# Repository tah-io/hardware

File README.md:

This repository consists of all the hardware design files for Tah

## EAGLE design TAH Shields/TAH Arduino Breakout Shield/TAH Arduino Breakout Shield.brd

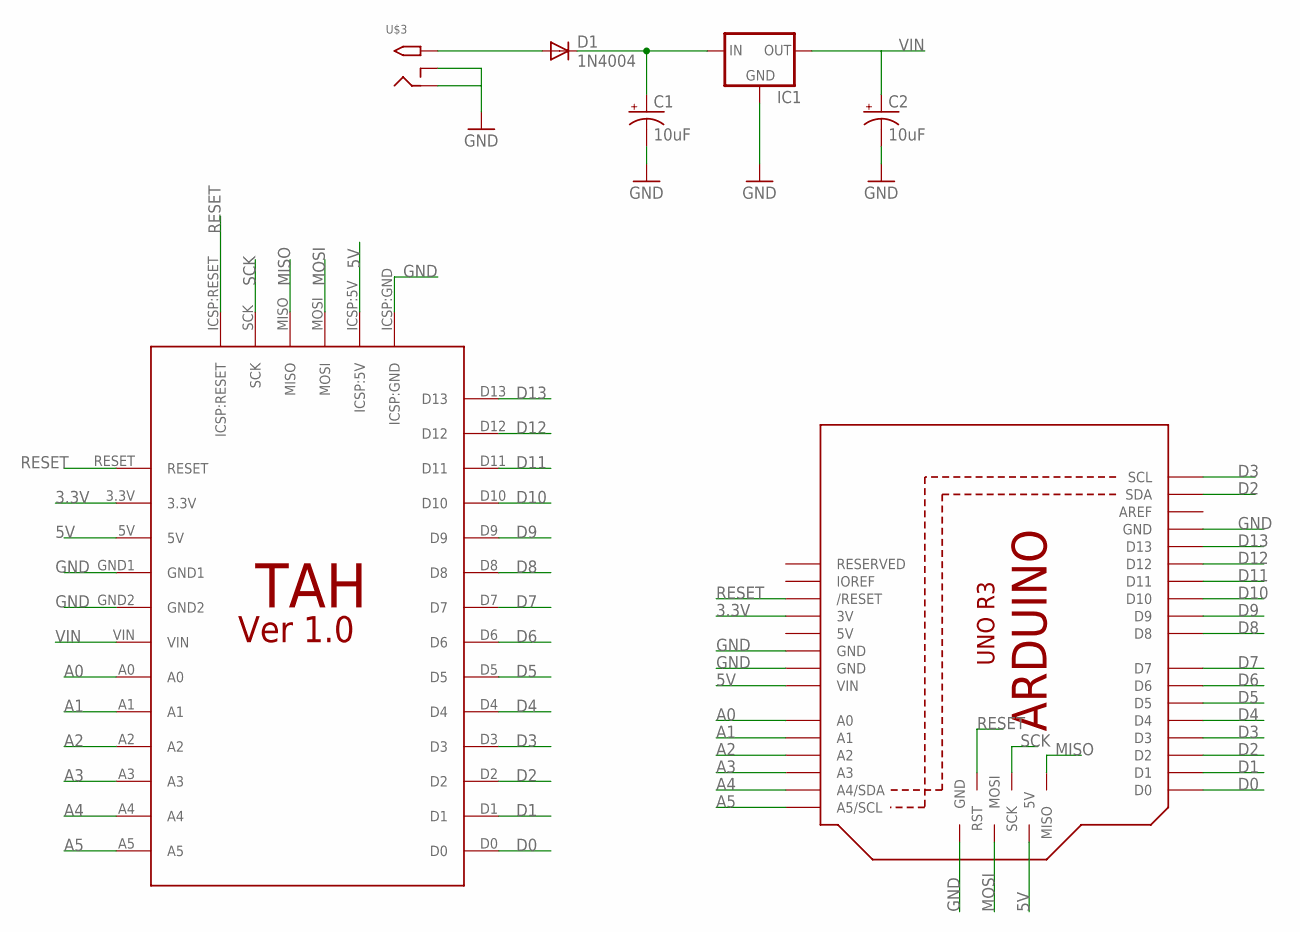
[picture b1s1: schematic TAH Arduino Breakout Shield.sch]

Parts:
C1, C2: 10uF; E2,5-6E
D1: 1N4004; DO41-10
IC1: V_REG_78XX-TO-220; TO-220-ALT
M1: ARDUINO_R3_ICSP_NODIM; ARDUINOR3_ICSP_NODIM
U$1: TAH_PIN_FOOTPRINT_VER1.0
U$3: 2.1MMJACKTHM; PJ-102A

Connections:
3.3V: M1.3V, U$1.3.3V
5V: M1.5V, M1.5V_ICSP (5V), M1.VIN, U$1.5V, U$1.ICSP:5V
A0: M1.A0, U$1.A0
A1: M1.A1, U$1.A1
A2: M1.A2, U$1.A2
A3: M1.A3, U$1.A3
A4: M1.A4 (A4/SDA), U$1.A4
A5: M1.A5 (A5/SCL), U$1.A5
D0: M1.D0, U$1.D0
D1: M1.D1, U$1.D1
D2: M1.D2, M1.SDA, U$1.D2
D3: M1.D3, M1.SCL, U$1.D3
D4: M1.D4, U$1.D4
D5: M1.D5, U$1.D5
D6: M1.D6, U$1.D6
D7: M1.D7, U$1.D7
D8: M1.D8, U$1.D8
D9: M1.D9, U$1.D9
D10: M1.D10, U$1.D10
D11: M1.D11, U$1.D11
D12: M1.D12, U$1.D12
D13: M1.D13, U$1.D13
GND: C1.-, C2.-, IC1.GND, M1.GND, M1.GND@1 (GND), M1.GND@2 (GND), M1.GND@3 (GND), U$1.GND1, U$1.GND2, U$1.ICSP:GND, U$3.RING, U$3.RING_SW
MISO: M1.MISO, U$1.MISO
MOSI: M1.MOSI, U$1.MOSI
unnamed: D1.A, U$3.TIP
unnamed: C1.+, D1.C, IC1.IN
RESET: M1.RESET (/RESET), M1.RESET_ICSP (RST), U$1.ICSP:RESET, U$1.RESET
SCK: M1.SCK, U$1.SCK
VIN: C2.+, IC1.OUT, U$1.VIN

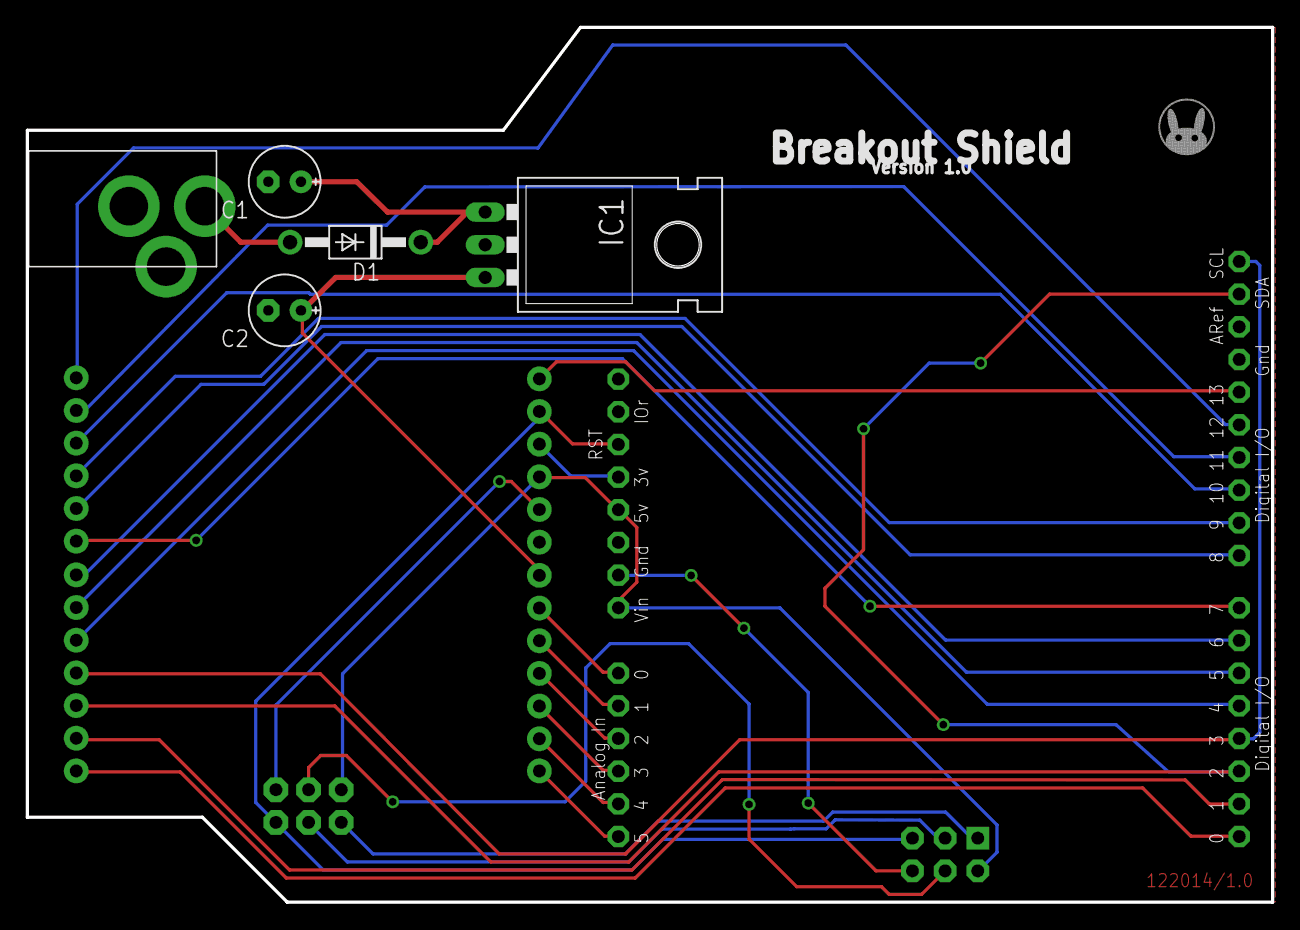
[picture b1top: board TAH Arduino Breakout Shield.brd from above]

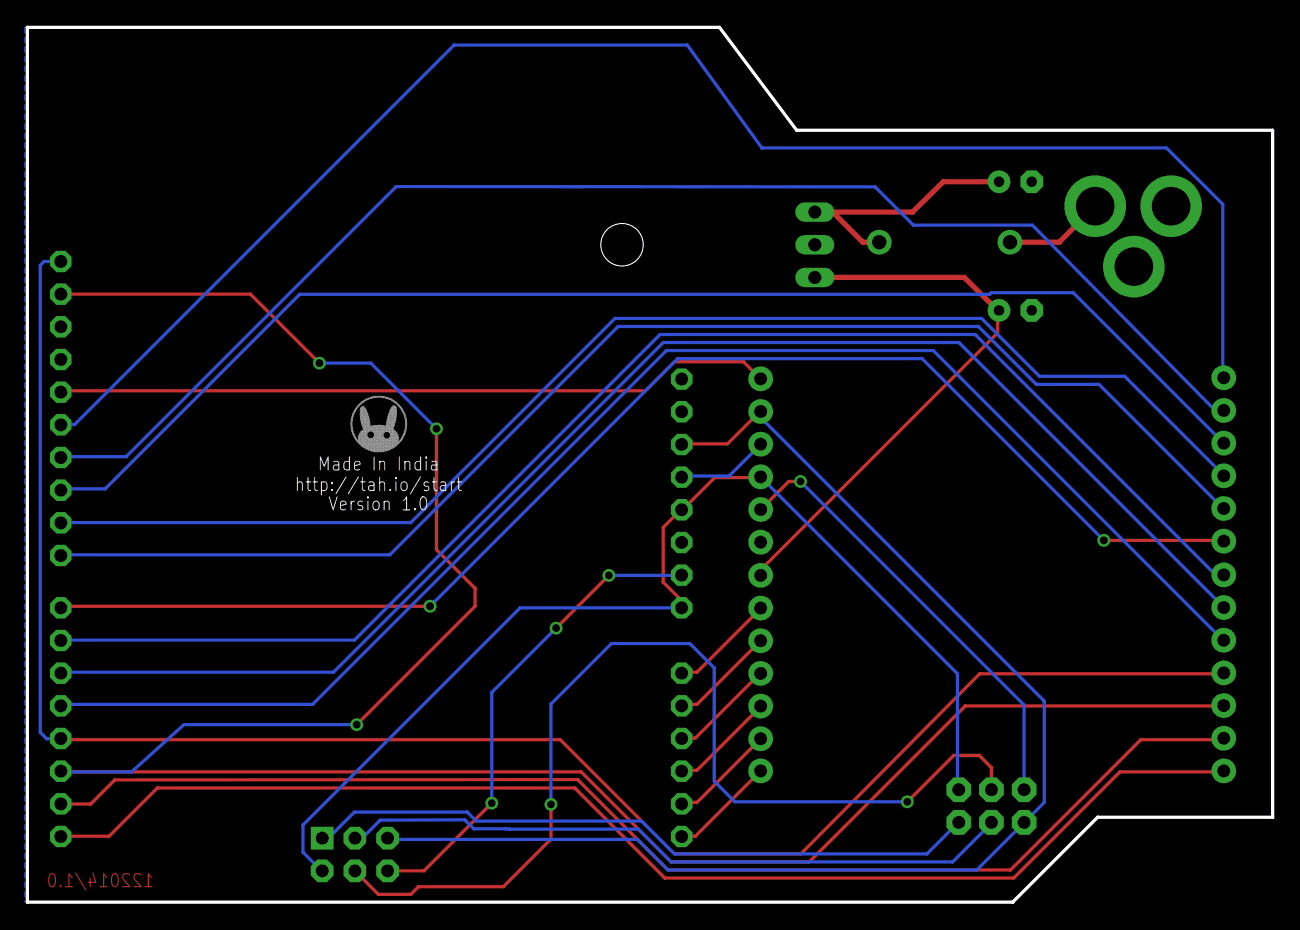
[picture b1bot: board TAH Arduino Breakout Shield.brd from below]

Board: 2 copper layers, 96.8 x 68.0 mm, 10 parts (2 on the bottom side), 30 nets.

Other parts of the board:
U$2, U$4: TAHLOGO
U$5: TAH_SILK_FLIPPED

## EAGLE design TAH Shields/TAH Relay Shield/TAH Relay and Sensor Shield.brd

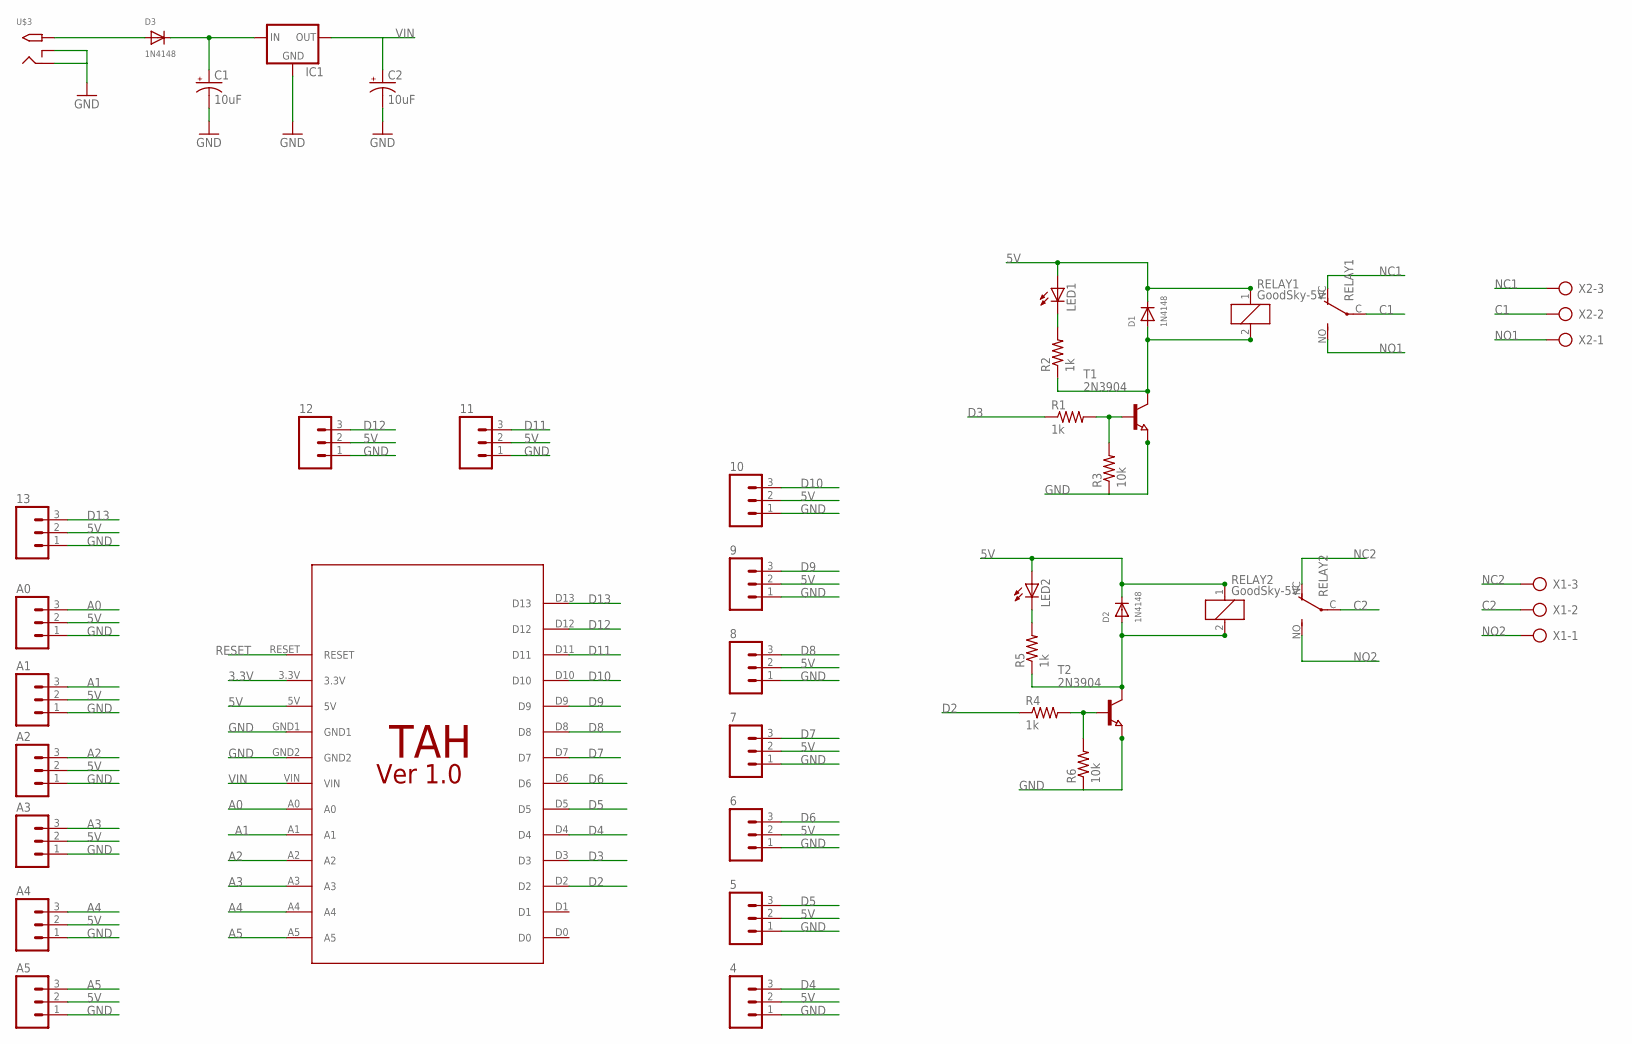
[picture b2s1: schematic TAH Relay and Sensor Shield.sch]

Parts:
4, 5, 6, 7, 8, 9, 10, 11, 12, 13: M03POLAR; MOLEX-1X3
A0, A1, A2, A3, A4, A5: M03POLAR; MOLEX-1X3
C1, C2: 10uF; E2,5-6E
D1, D2, D3: 1N4148; SMADIODE
IC1: V_REG_78XX-TO-220; TO-220-ALT
LED1, LED2: LEDSMT1206; 1206
R1, R2, R4, R5: 1k; R1206
R3, R6: 10k; R1206
RELAY1, RELAY2: GoodSky-5V; CQ1
T1, T2: 2N3904; SOT23
U$1: TAH_PIN_FOOTPRINT_WITHOUT_ICSP_VER1.0; FOOTPRINT_WITHOUT_ICSP
U$3: 2.1MMJACKTHM; PJ-102A
X1, X2: AK300/3

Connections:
3.3V: U$1.3.3V
5V: 4.2, 5.2, 6.2, 7.2, 8.2, 9.2, 10.2, 11.2, 12.2, 13.2, A0.2, A1.2, A2.2, A3.2, A4.2, A5.2, D1.C, D2.C, LED1.A, LED2.A, RELAY1.1, RELAY2.1, U$1.5V
A0: A0.3, U$1.A0
A1: A1.3, U$1.A1
A2: A2.3, U$1.A2
A3: A3.3, U$1.A3
A4: A4.3, U$1.A4
A5: A5.3, U$1.A5
C1: RELAY1.C, X2.2
C2: RELAY2.C, X1.2
D2: R4.1, U$1.D2
D3: R1.1, U$1.D3
D4: 4.3, U$1.D4
D5: 5.3, U$1.D5
D6: 6.3, U$1.D6
D7: 7.3, U$1.D7
D8: 8.3, U$1.D8
D9: 9.3, U$1.D9
D10: 10.3, U$1.D10
D11: 11.3, U$1.D11
D12: 12.3, U$1.D12
D13: 13.3, U$1.D13
GND: 4.1, 5.1, 6.1, 7.1, 8.1, 9.1, 10.1, 11.1, 12.1, 13.1, A0.1, A1.1, A2.1, A3.1, A4.1, A5.1, C1.-, C2.-, IC1.GND, R3.1, R6.1, T1.2 (E), T2.2 (E), U$1.GND1, U$1.GND2, U$3.RING, U$3.RING_SW
unnamed: D2.A, R5.1, RELAY2.2, T2.3 (C)
unnamed: R4.2, R6.2, T2.1 (B)
unnamed: LED2.C, R5.2
unnamed: D3.A, U$3.TIP
unnamed: C1.+, D3.C, IC1.IN
unnamed: D1.A, R2.1, RELAY1.2, T1.3 (C)
unnamed: R1.2, R3.2, T1.1 (B)
unnamed: LED1.C, R2.2
NC1: RELAY1.NC (O), X2.3
NC2: RELAY2.NC (O), X1.3
NO1: RELAY1.NO (S), X2.1
NO2: RELAY2.NO (S), X1.1
RESET: U$1.RESET
VIN: C2.+, IC1.OUT, U$1.VIN

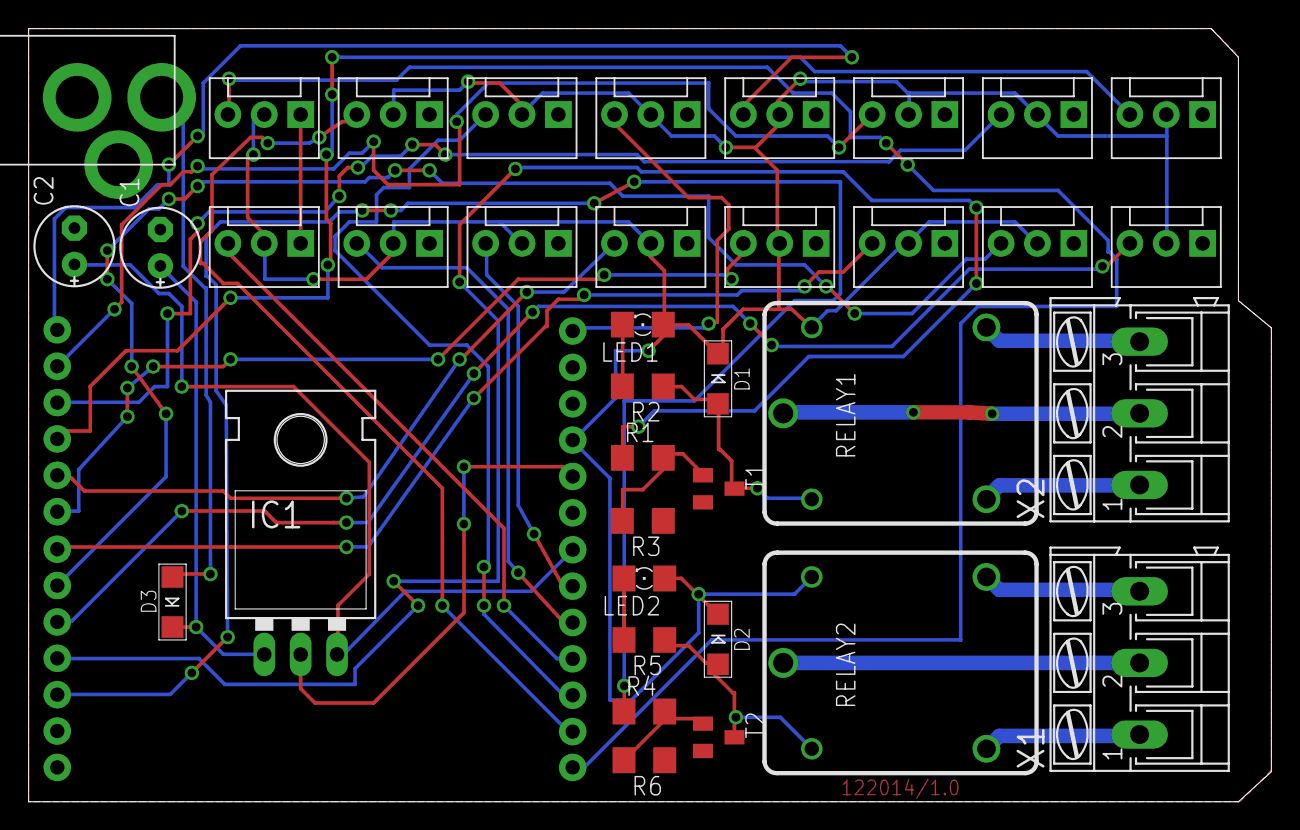
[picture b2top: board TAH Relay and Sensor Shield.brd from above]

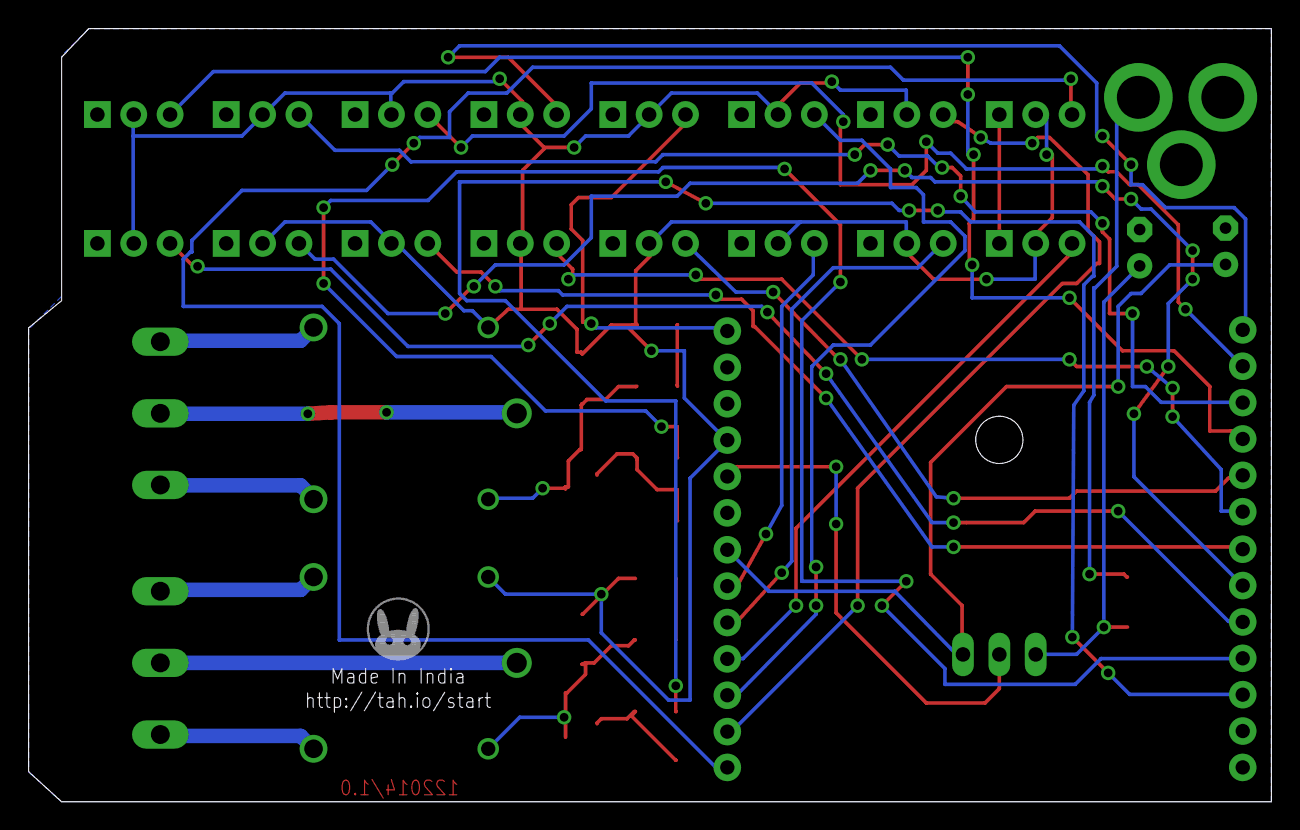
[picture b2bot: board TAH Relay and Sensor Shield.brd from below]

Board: 2 copper layers, 86.8 x 54.0 mm, 40 parts (2 on the bottom side), 35 nets.

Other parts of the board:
U$2: TAHLOGO
U$4: TAH_SILK_FLIPPED

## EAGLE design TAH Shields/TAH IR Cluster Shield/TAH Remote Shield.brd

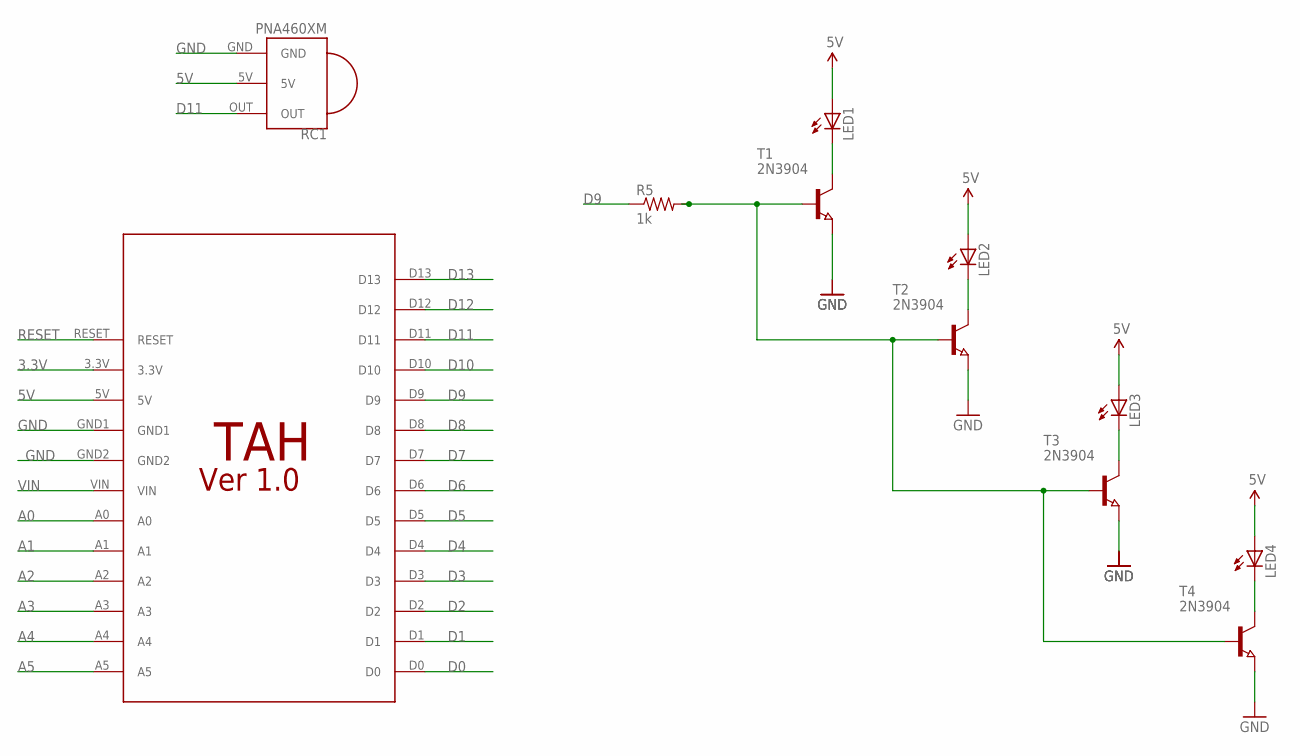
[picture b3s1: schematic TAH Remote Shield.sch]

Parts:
LED1, LED2, LED3, LED4: LED5MM
R5: 1k; M1206
RC1: PNA460XM
T1, T2, T3, T4: 2N3904; SOT23
U$2: TAH_PIN_FOOTPRINT_WITHOUT_ICSP_VER1.0

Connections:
3.3V: U$2.3.3V
5V: LED1.A, LED2.A, LED3.A, LED4.A, RC1.5V, U$2.5V
A0: U$2.A0
A1: U$2.A1
A2: U$2.A2
A3: U$2.A3
A4: U$2.A4
A5: U$2.A5
D0: U$2.D0
D1: U$2.D1
D2: U$2.D2
D3: U$2.D3
D4: U$2.D4
D5: U$2.D5
D6: U$2.D6
D7: U$2.D7
D8: U$2.D8
D9: R5.1, U$2.D9
D10: U$2.D10
D11: RC1.OUT, U$2.D11
D12: U$2.D12
D13: U$2.D13
GND: RC1.GND, T1.2 (E), T2.2 (E), T3.2 (E), T4.2 (E), U$2.GND1, U$2.GND2
unnamed: LED1.K (C), T1.3 (C)
unnamed: LED2.K (C), T2.3 (C)
unnamed: LED4.K (C), T4.3 (C)
unnamed: LED3.K (C), T3.3 (C)
unnamed: R5.2, T1.1 (B), T2.1 (B), T3.1 (B), T4.1 (B)
RESET: U$2.RESET
VIN: U$2.VIN

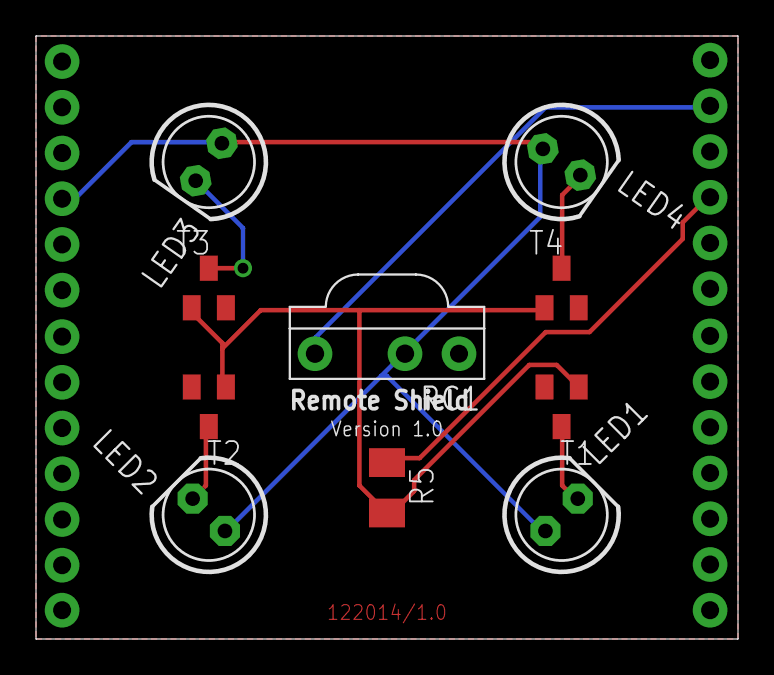
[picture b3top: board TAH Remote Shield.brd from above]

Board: 2 copper layers, 39.0 x 33.5 mm, 13 parts (1 on the bottom side), 9 nets.

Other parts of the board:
U$1: TAHLOGO
U$4: TAH_PIN_FOOTPRINT_WITHOUT_ICSP_VERS1.0_SILK

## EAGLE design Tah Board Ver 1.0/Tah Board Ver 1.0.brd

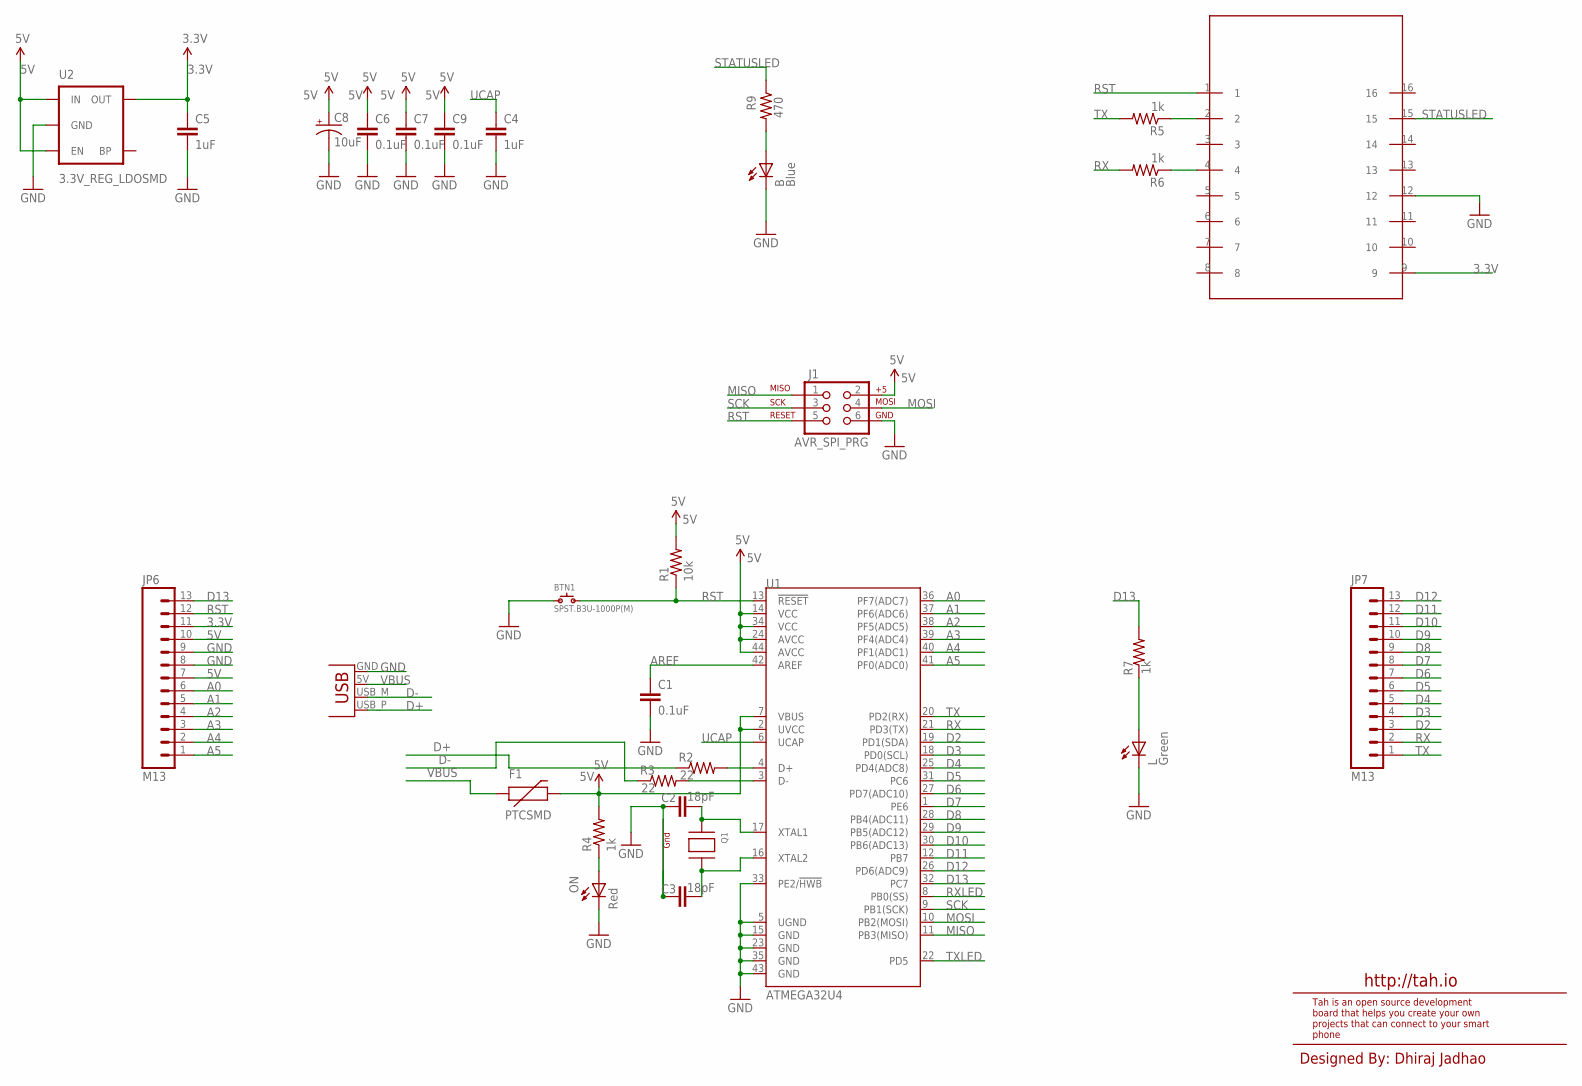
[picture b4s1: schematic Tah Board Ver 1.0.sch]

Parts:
B: Blue; 1206
BLE: HM-11HM11; BC05B-SMD
BTN1: SPST.B3U-1000P(M); B3U-1000P(M)
C1, C6, C7, C9: 0.1uF; 1206
C2, C3: 18pF; 1206
C4, C5: 1uF; 1206
C8: 10uF; EIA3216
F1: PTCSMD; PTC-1206
J1: AVR_SPI_PRG; 2X3
JP2: USBPCB; USB-A-PCB
JP6, JP7: M13; 1X13
L: Green; 1206
ON: Red; 1206
Q1: XTAL-4-3225; NX3225
R1: 10k; 1206
R2, R3: 22; 1206
R4, R5, R6, R7: 1k; 1206
R9: 470; 1206
U1: ATMEGA32U4; SPARKFUN-DIGITALIC_QFN-44-NOPAD
U2: 3.3V_REG_LDOSMD; SOT23-5

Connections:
3.3V: BLE.9, C5.1, JP6.11, U2.5 (OUT)
5V: C6.1, C7.1, C8.A (+), C9.1, F1.2, J1.2, JP6.7, JP6.10, R1.2, R4.2, U1.2 (UVCC), U1.7 (VBUS), U1.14 (VCC), U1.24 (AVCC), U1.34 (VCC), U1.44 (AVCC), U2.1 (IN), U2.3 (EN)
A0: JP6.6, U1.36 (PF7(ADC7))
A1: JP6.5, U1.37 (PF6(ADC6))
A2: JP6.4, U1.38 (PF5(ADC5))
A3: JP6.3, U1.39 (PF4(ADC4))
A4: JP6.2, U1.40 (PF1(ADC1))
A5: JP6.1, U1.41 (PF0(ADC0))
AREF: C1.1, U1.42 (AREF)
D2: JP7.3, U1.19 (PD1(SDA))
D3: JP7.4, U1.18 (PD0(SCL))
D4: JP7.5, U1.25 (PD4(ADC8))
D5: JP7.6, U1.31 (PC6)
D6: JP7.7, U1.27 (PD7(ADC10))
D7: JP7.8, U1.1 (PE6)
D8: JP7.9, U1.28 (PB4(ADC11))
D9: JP7.10, U1.29 (PB5(ADC12))
D10: JP7.11, U1.30 (PB6(ADC13))
D11: JP7.12, U1.12 (PB7)
D12: JP7.13, U1.26 (PD6(ADC9))
D13: JP6.13, R7.2, U1.32 (PC7)
D+: JP2.USB_P (D+), R2.1
D-: JP2.USB_M (D-), R3.1
GND: B.C, BLE.12, BTN1.1, C1.2, C2.1, C3.1, C4.2, C5.2, C6.2, C7.2, C8.C (-), C9.2, J1.6, JP2.GND, JP6.8, JP6.9, L.C, ON.C, Q1.2 (G2), Q1.4 (G1), U1.5 (UGND), U1.15 (GND), U1.23 (GND), U1.33 (PE2/!HWB), U1.35 (GND), U1.43 (GND), U2.2 (GND)
MISO: J1.1, U1.11 (PB3(MISO))
MOSI: J1.4, U1.10 (PB2(MOSI))
unnamed: L.A, R7.1
unnamed: C2.2, Q1.1 (X1), U1.17 (XTAL1)
unnamed: C3.2, Q1.3 (X2), U1.16 (XTAL2)
unnamed: BLE.2, R5.1
unnamed: BLE.4, R6.1
unnamed: R2.2, U1.4 (D+)
unnamed: R3.2, U1.3 (D-)
unnamed: ON.A, R4.1
unnamed: B.A, R9.2
RST: BLE.1, BTN1.2, J1.5, JP6.12, R1.1, U1.13 (!RESET)
RX: JP7.2, R6.2, U1.21 (PD3(TX))
RXLED: U1.8 (PB0(SS))
SCK: J1.3, U1.9 (PB1(SCK))
STATUSLED: BLE.15, R9.1
TX: JP7.1, R5.2, U1.20 (PD2(RX))
TXLED: U1.22 (PD5)
UCAP: C4.1, U1.6 (UCAP)
VBUS: F1.1, JP2.5V (VBUS)

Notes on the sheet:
Designed By: Dhiraj Jadhao
http://tah.io
Tah is an open source development board that helps you create your own projects that can connect to your smart phone

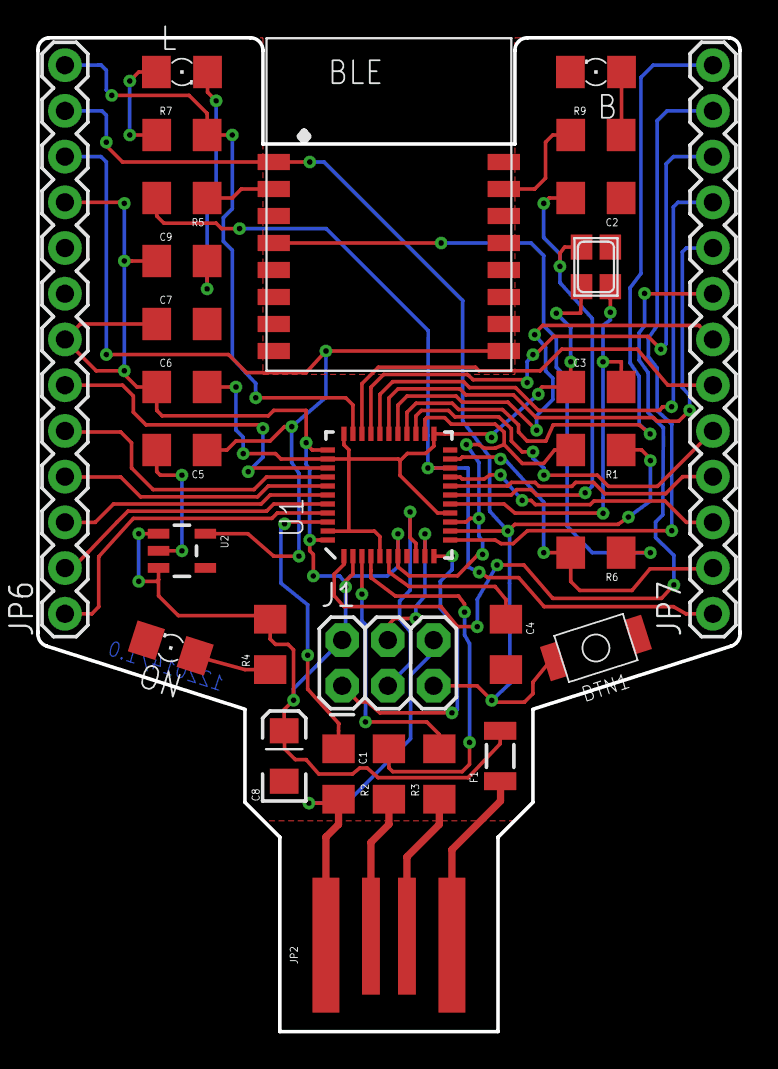
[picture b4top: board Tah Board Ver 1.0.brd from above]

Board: 2 copper layers, 39.0 x 55.2 mm, 31 parts (1 on the bottom side), 42 nets.

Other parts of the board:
U$1: TAHLOGO

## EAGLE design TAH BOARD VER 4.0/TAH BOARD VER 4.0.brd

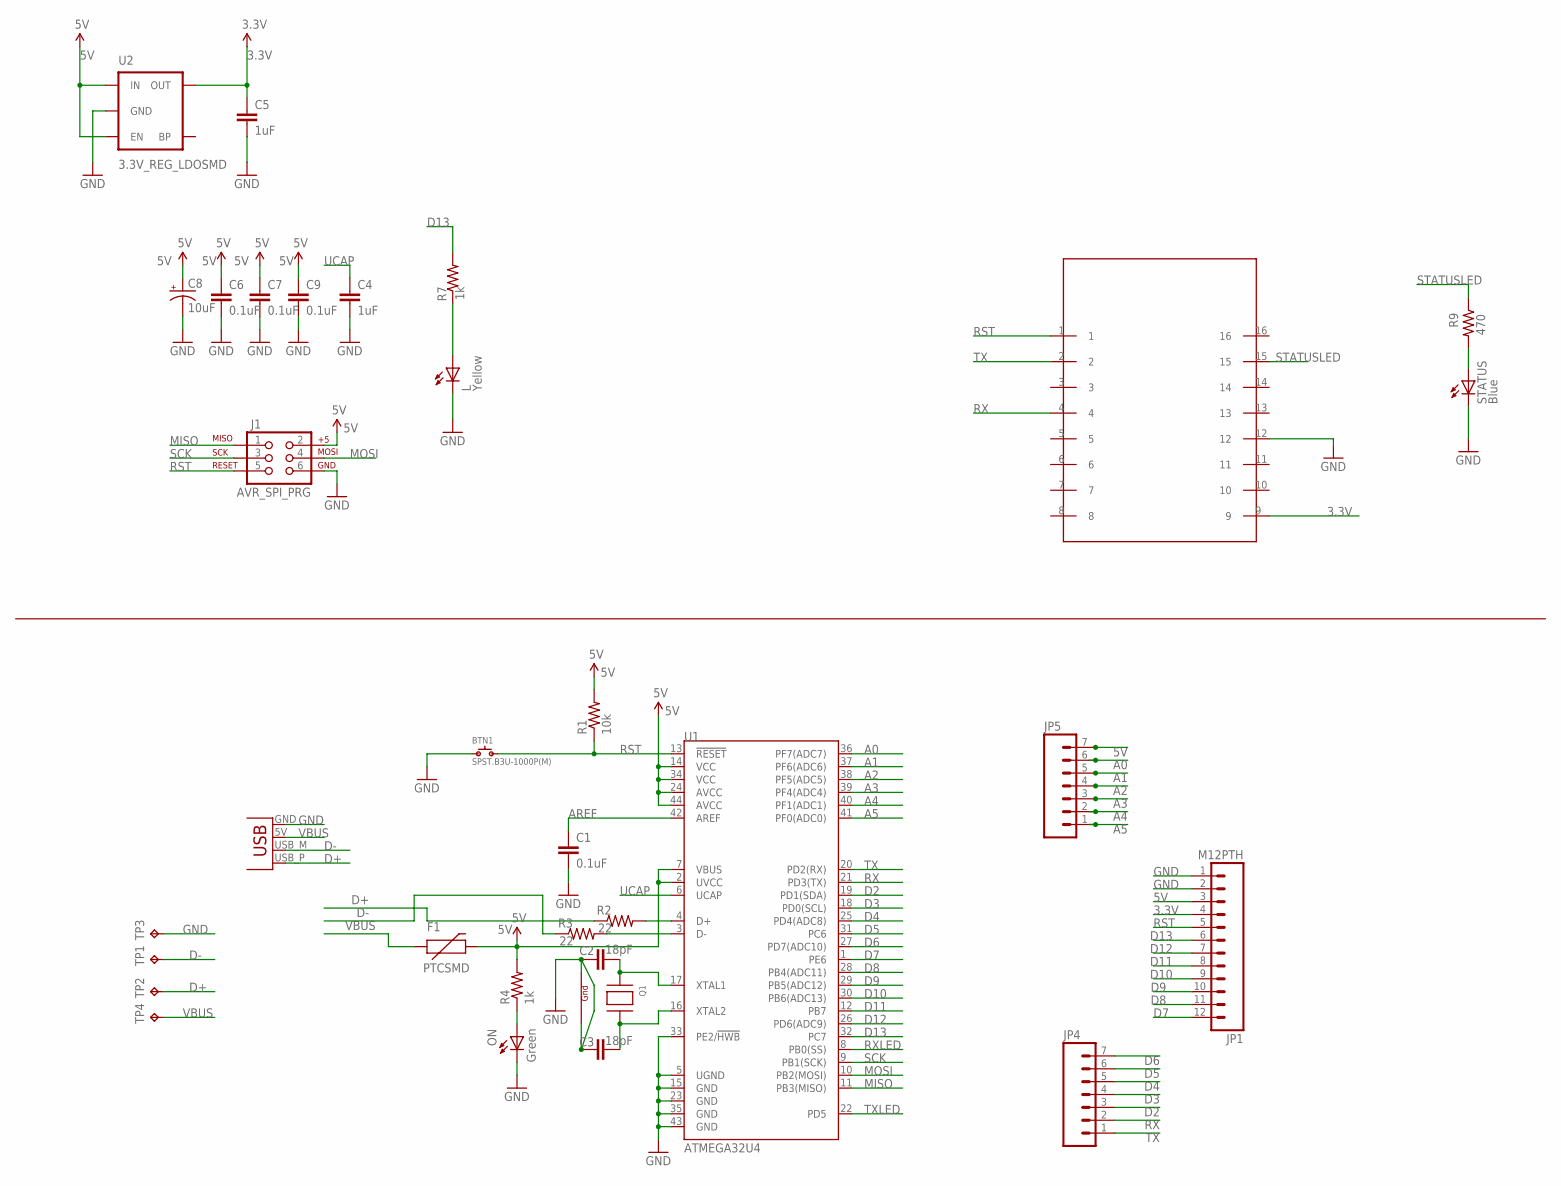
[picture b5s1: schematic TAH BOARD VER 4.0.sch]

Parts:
BLE: HM-11HM11; BC05B-SMD
BTN1: SPST.B3U-1000P(M); B3U-1000P(M)
C1, C6, C7, C9: 0.1uF; 1206
C2, C3: 18pF; 1206
C4, C5: 1uF; 1206
C8: 10uF; EIA3216
F1: PTCSMD; PTC-1206
J1: AVR_SPI_PRG; 2X3
JP1: M12PTH; 1X12
JP2: USBPCB; USB-A-PCB
JP4, JP5: M07; 1X07
L: Yellow; 1206
ON: Green; 1206
Q1: XTAL-4-3225; NX3225
R1: 10k; 1206
R2, R3: 22; 1206
R4, R7: 1k; 1206
R9: 470; 1206
STATUS: Blue; 1206
TP1, TP2, TP3, TP4: TPTP11SQ; TP11SQ
U1: ATMEGA32U4; SPARKFUN-DIGITALIC_TQFP44
U2: 3.3V_REG_LDOSMD; SOT23-5

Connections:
3.3V: BLE.9, C5.1, JP1.4, U2.5 (OUT)
5V: C6.1, C7.1, C8.A (+), C9.1, F1.2, J1.2, JP1.3, JP5.7, R1.2, R4.2, U1.2 (UVCC), U1.7 (VBUS), U1.14 (VCC), U1.24 (AVCC), U1.34 (VCC), U1.44 (AVCC), U2.1 (IN), U2.3 (EN)
A0: JP5.6, U1.36 (PF7(ADC7))
A1: JP5.5, U1.37 (PF6(ADC6))
A2: JP5.4, U1.38 (PF5(ADC5))
A3: JP5.3, U1.39 (PF4(ADC4))
A4: JP5.2, U1.40 (PF1(ADC1))
A5: JP5.1, U1.41 (PF0(ADC0))
AREF: C1.1, U1.42 (AREF)
D2: JP4.3, U1.19 (PD1(SDA))
D3: JP4.4, U1.18 (PD0(SCL))
D4: JP4.5, U1.25 (PD4(ADC8))
D5: JP4.6, U1.31 (PC6)
D6: JP4.7, U1.27 (PD7(ADC10))
D7: JP1.12, U1.1 (PE6)
D8: JP1.11, U1.28 (PB4(ADC11))
D9: JP1.10, U1.29 (PB5(ADC12))
D10: JP1.9, U1.30 (PB6(ADC13))
D11: JP1.8, U1.12 (PB7)
D12: JP1.7, U1.26 (PD6(ADC9))
D13: JP1.6, R7.2, U1.32 (PC7)
D+: JP2.USB_P (D+), R2.1, TP2.TP
D-: JP2.USB_M (D-), R3.1, TP1.TP
GND: BLE.12, BTN1.1, C1.2, C2.1, C3.1, C4.2, C5.2, C6.2, C7.2, C8.C (-), C9.2, J1.6, JP1.1, JP1.2, JP2.GND, L.C, ON.C, Q1.2 (G2), Q1.4 (G1), STATUS.C, TP3.TP, U1.5 (UGND), U1.15 (GND), U1.23 (GND), U1.33 (PE2/!HWB), U1.35 (GND), U1.43 (GND), U2.2 (GND)
MISO: J1.1, U1.11 (PB3(MISO))
MOSI: J1.4, U1.10 (PB2(MOSI))
unnamed: L.A, R7.1
unnamed: C2.2, Q1.1 (X1), U1.17 (XTAL1)
unnamed: C3.2, Q1.3 (X2), U1.16 (XTAL2)
unnamed: R2.2, U1.4 (D+)
unnamed: R3.2, U1.3 (D-)
unnamed: ON.A, R4.1
unnamed: R9.2, STATUS.A
RST: BLE.1, BTN1.2, J1.5, JP1.5, R1.1, U1.13 (!RESET)
RX: BLE.4, JP4.2, U1.21 (PD3(TX))
RXLED: U1.8 (PB0(SS))
SCK: J1.3, U1.9 (PB1(SCK))
STATUSLED: BLE.15, R9.1
TX: BLE.2, JP4.1, U1.20 (PD2(RX))
TXLED: U1.22 (PD5)
UCAP: C4.1, U1.6 (UCAP)
VBUS: F1.1, JP2.5V (VBUS), TP4.TP

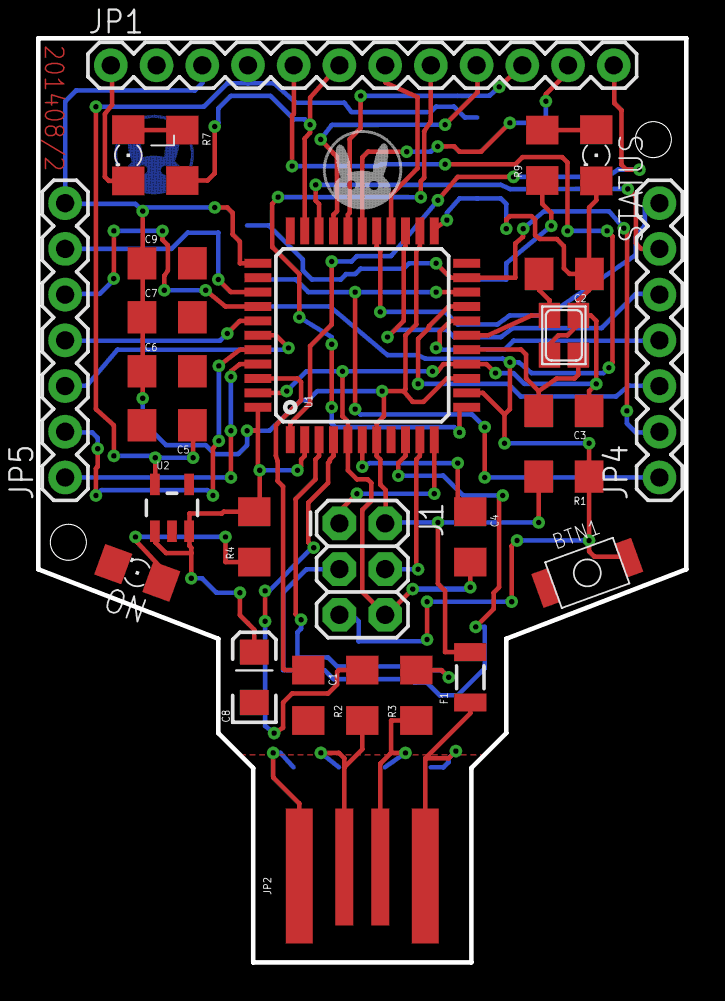
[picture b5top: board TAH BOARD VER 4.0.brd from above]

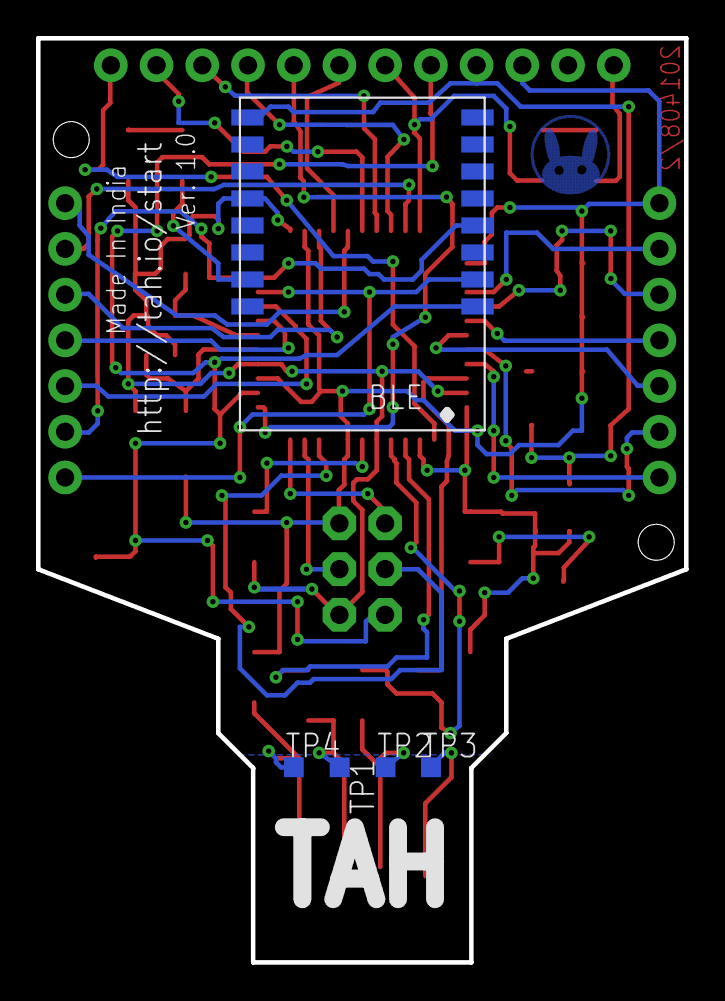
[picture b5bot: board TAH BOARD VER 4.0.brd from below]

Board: 2 copper layers, 36.0 x 51.3 mm, 35 parts (5 on the bottom side), 40 nets.

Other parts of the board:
U$1: TAHLOGO
U$3: TAH_LOGO_ETCHED

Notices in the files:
parts and their libraries:
FTDI modifed: Licensing: CC v3.0 Share-Alike You are welcome to use this library for commercial purposes.
SparkFun-Aesthetics: Licensing: Creative Commons ShareAlike 4.0 International - https://creativecommons.org/licenses/by-sa/4.0
